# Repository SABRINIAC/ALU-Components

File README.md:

# ALU Modules

| What it is

This project is the collection of PCB that make up all of the Intel 8080 (Which is what my CPU is based on) ALU's functionality. \
It contains modules for an 8 bit adder, subtractor, AND, OR, XOR, rotate left, and rotate right. Also it has a NOT module for the CMA instruction, which inverts all the bits in the accumulator register. \
Also coincidentally there are 8 modules, which will make multiplexing to choose data lines really nice and easy! If I ever decide to create the module for DAA, which I don't have atm because im kinda lazy and I think it'll be seldom used, I can alway make the NOT module not on the multiplex because it is exclusively used to invert the accumulator register for CMA and nothing else.

| Why I made it

Most of my reasoning can be found in the [RAM Module readme](https://github.com/SABRINIAC/DelayLineRAM-ShiftRegister) but aside from that I made this so I can do what CPUs are really good for. Math! These modules alone, making up the ALU, accounts for 96 out of the 255 instructions my CPU needs. Over a third at 37.6%! \
I don't think another project will get even close to implementing that many instructions! They would need a combination of making registers, and routing on the motherboard; which tbf the ALU also needs that. \

Also, making a computer out of pure transistors sounds really cool! Getting to learn how to make logic gates with them was fun, but I don't think I've fully committed how they precisely work to my brain yet... maybe later on in this project.

| Pictures

| BOM + Quantity

You can see a greater breakdown in BOM.md, but here the table breakdown
| Part Name | Count |
|-----------|-------|
| 1x2 Male Pin Headers | 99 |
| 2N2222 NPN Transistors | 432 |
| 1kΩ Resistor 0603 SMD | 670 |
| Adder PCB | 1 |
| Subtractor PCB | 1 |
| AND PCB | 1 |
| XOR PCB | 1 |
| OR PCB | 1 |
| NOT PCB | 1 |
| Rotate Right PCB | 1 |
| Rotate Left PCB | 1 |

# Built Modules

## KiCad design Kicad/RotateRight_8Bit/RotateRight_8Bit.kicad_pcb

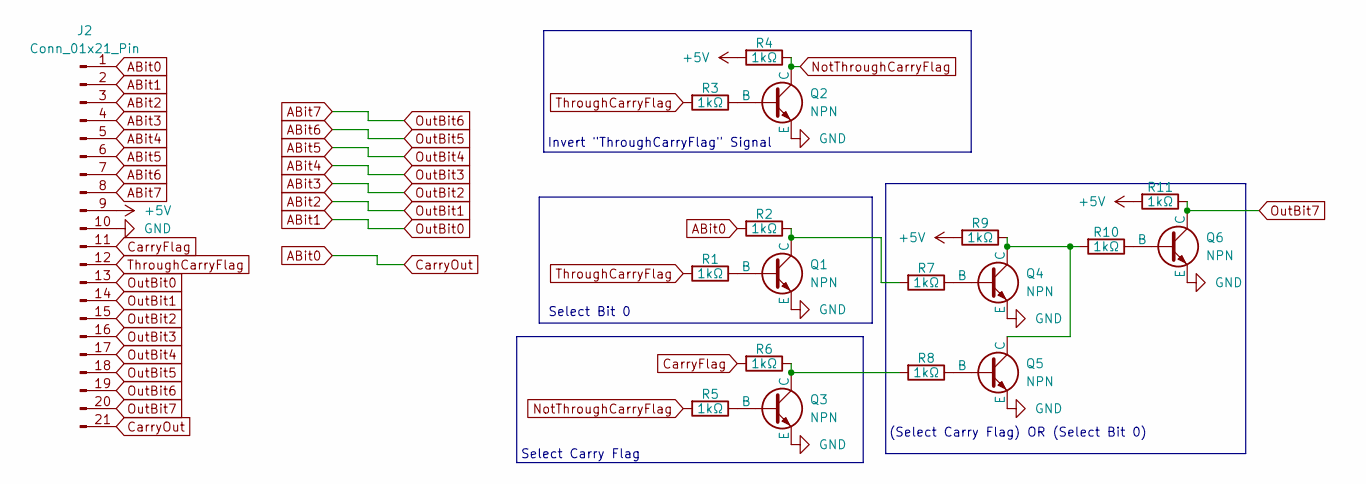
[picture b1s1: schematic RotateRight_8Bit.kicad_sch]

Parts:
J2: Conn_01x21_Pin; PinHeader_1x21_P2.54mm_Horizontal
Q1, Q2, Q3, Q4, Q5, Q6: NPN; TO-92
R1, R2, R3, R4, R5, R6, R7, R8, R9, R10, R11: 1kΩ; R_0603_1608Metric

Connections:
+5V: J2.9, R4.2, R9.2, R11.2
ABit0: J2.1, J2.21, R2.2
ABit1: J2.2, J2.13
ABit2: J2.3, J2.14
ABit3: J2.4, J2.15
ABit4: J2.5, J2.16
ABit5: J2.6, J2.17
ABit6: J2.7, J2.18
ABit7: J2.8, J2.19
CarryFlag: J2.11, R6.2
GND: J2.10, Q1.3 (E), Q2.3 (E), Q3.3 (E), Q4.3 (E), Q5.3 (E), Q6.3 (E)
unnamed: Q1.2 (B), R1.1
unnamed: Q1.1 (C), R2.1, R7.2
unnamed: Q2.2 (B), R3.1
unnamed: Q3.2 (B), R5.1
unnamed: Q3.1 (C), R6.1, R8.2
unnamed: Q4.2 (B), R7.1
unnamed: Q4.1 (C), Q5.1 (C), R9.1, R10.2
unnamed: Q5.2 (B), R8.1
unnamed: Q6.2 (B), R10.1
NotThroughCarryFlag: Q2.1 (C), R4.1, R5.2
OutBit7: J2.20, Q6.1 (C), R11.1
ThroughCarryFlag: J2.12, R1.2, R3.2

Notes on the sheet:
(Select Carry Flag) OR (Select Bit 0)
Select Bit 0
Select Carry Flag
Invert "ThroughCarryFlag" Signal

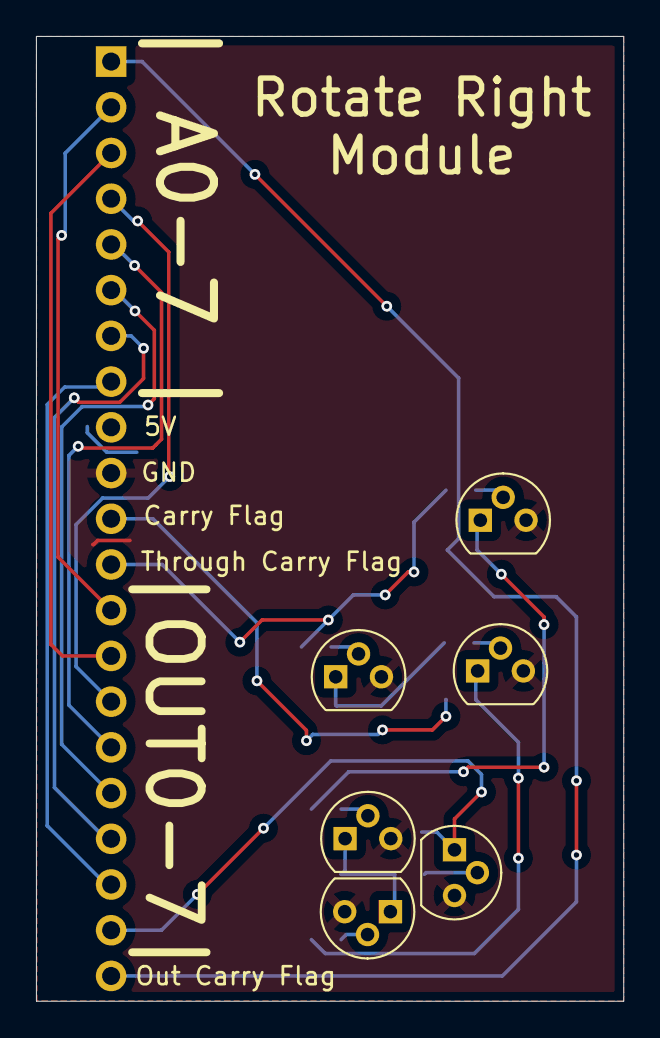
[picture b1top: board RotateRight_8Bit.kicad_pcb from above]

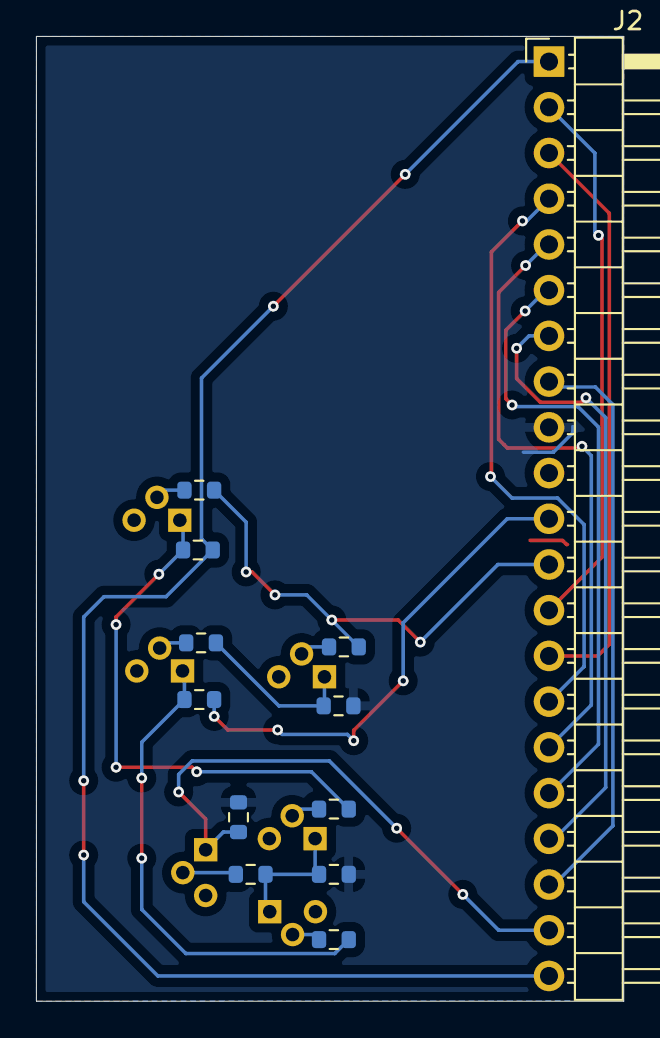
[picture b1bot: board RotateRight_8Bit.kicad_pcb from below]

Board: 2 copper layers, 32.6 x 53.6 mm, 18 parts (12 on the bottom side), 23 nets.

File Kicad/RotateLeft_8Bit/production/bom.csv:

Designator,Footprint,Quantity,Value,LCSC Part #
J2,PinHeader_1x21_P2.54mm_Horizontal,1,Conn_01x21_Pin,
"Q1, Q2, Q3, Q4, Q5, Q6",TO-92,6,NPN,
"R1, R10, R11, R2, R3, R4, R5, R6, R7, R8, R9",0603,11,1kΩ,

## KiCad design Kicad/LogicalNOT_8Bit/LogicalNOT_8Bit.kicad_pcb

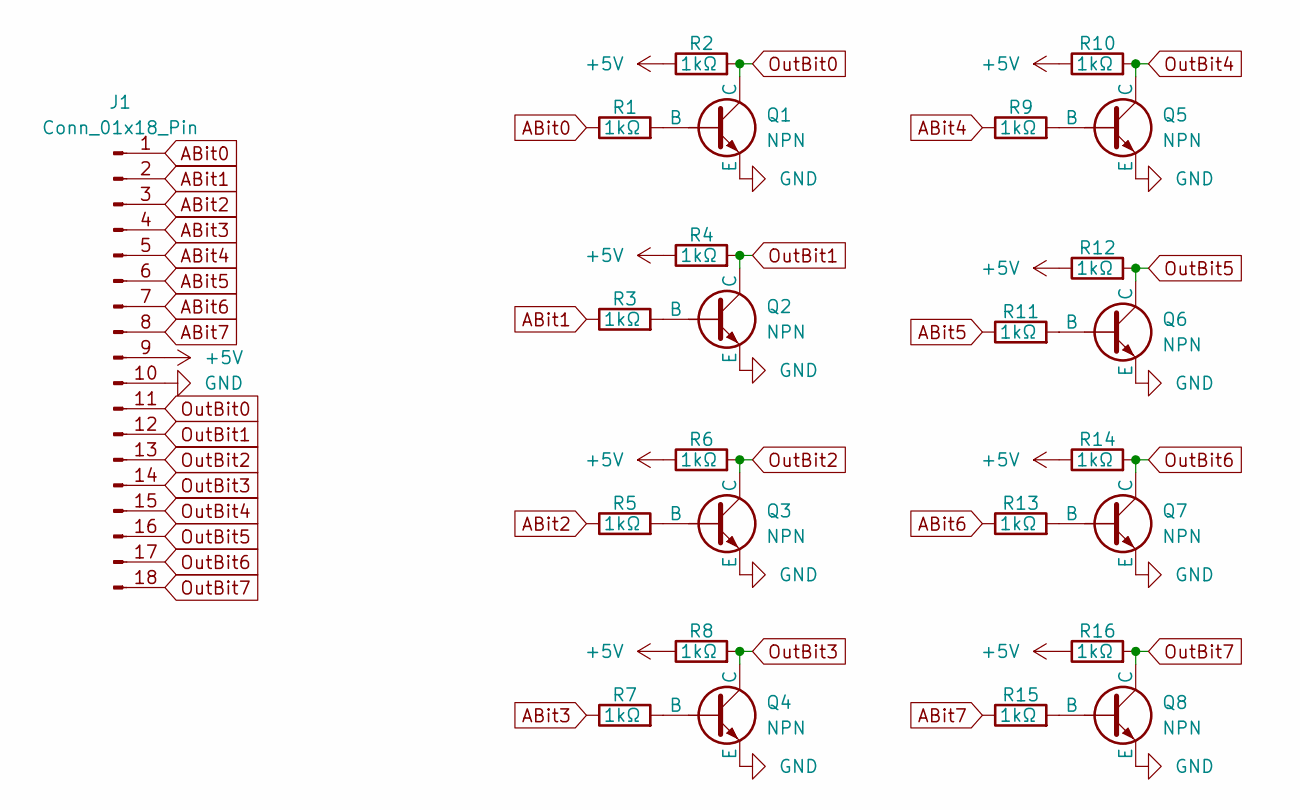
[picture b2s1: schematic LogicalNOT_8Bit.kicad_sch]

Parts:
J1: Conn_01x18_Pin; PinHeader_1x18_P2.54mm_Horizontal
Q1, Q2, Q3, Q4, Q5, Q6, Q7, Q8: NPN; TO-92
R1, R2, R3, R4, R5, R6, R7, R8, R9, R10, R11, R12, R13, R14, R15, R16: 1kΩ; R_0603_1608Metric

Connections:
+5V: J1.9, R2.1, R4.1, R6.1, R8.1, R10.1, R12.1, R14.1, R16.1
ABit0: J1.1, R1.1
ABit1: J1.2, R3.1
ABit2: J1.3, R5.1
ABit3: J1.4, R7.1
ABit4: J1.5, R9.1
ABit5: J1.6, R11.1
ABit6: J1.7, R13.1
ABit7: J1.8, R15.1
GND: J1.10, Q1.3 (E), Q2.3 (E), Q3.3 (E), Q4.3 (E), Q5.3 (E), Q6.3 (E), Q7.3 (E), Q8.3 (E)
unnamed: Q1.2 (B), R1.2
unnamed: Q2.2 (B), R3.2
unnamed: Q3.2 (B), R5.2
unnamed: Q4.2 (B), R7.2
unnamed: Q5.2 (B), R9.2
unnamed: Q6.2 (B), R11.2
unnamed: Q7.2 (B), R13.2
unnamed: Q8.2 (B), R15.2
OutBit0: J1.11, Q1.1 (C), R2.2
OutBit1: J1.12, Q2.1 (C), R4.2
OutBit2: J1.13, Q3.1 (C), R6.2
OutBit3: J1.14, Q4.1 (C), R8.2
OutBit4: J1.15, Q5.1 (C), R10.2
OutBit5: J1.16, Q6.1 (C), R12.2
OutBit6: J1.17, Q7.1 (C), R14.2
OutBit7: J1.18, Q8.1 (C), R16.2

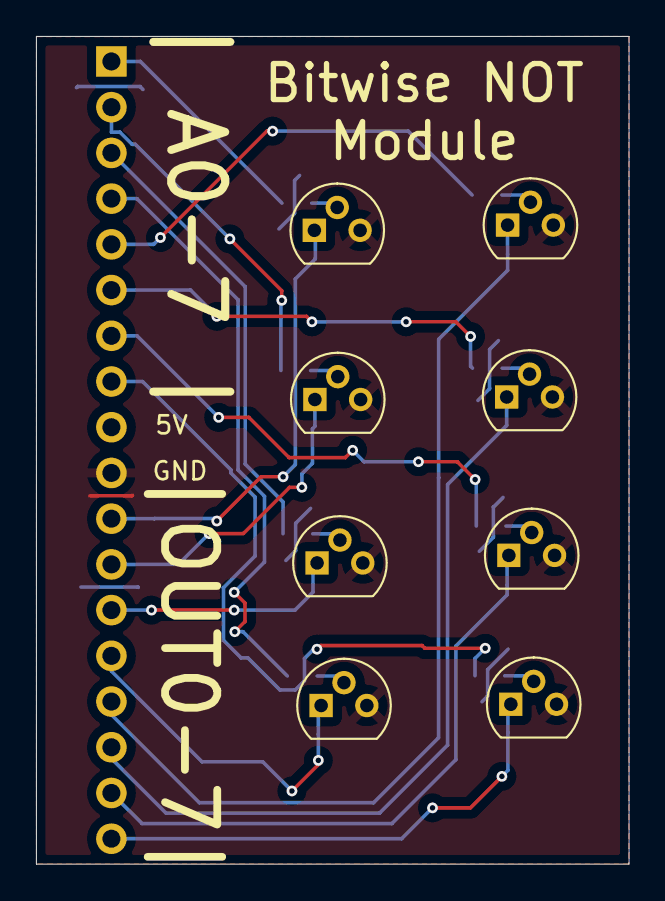
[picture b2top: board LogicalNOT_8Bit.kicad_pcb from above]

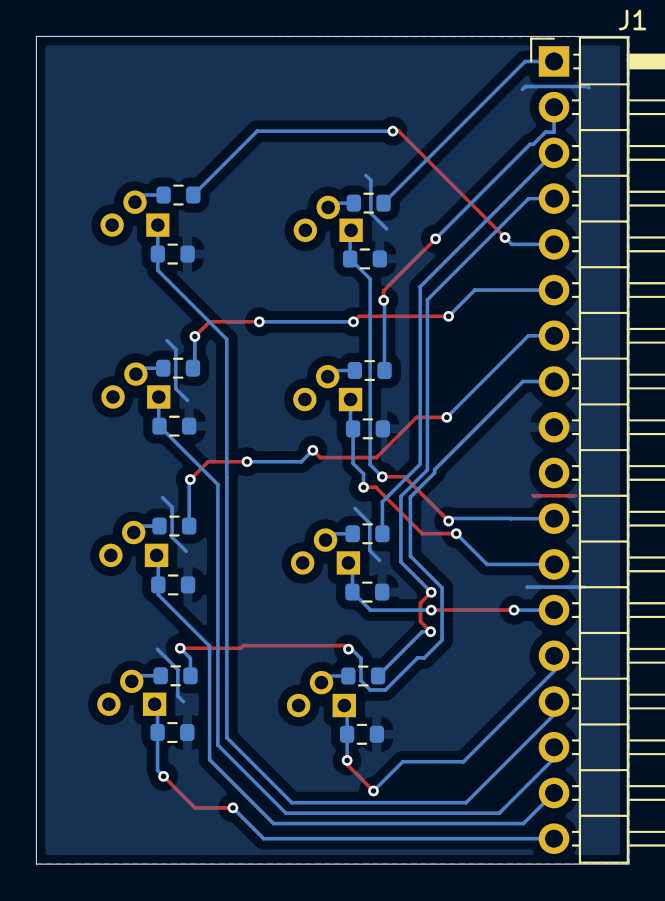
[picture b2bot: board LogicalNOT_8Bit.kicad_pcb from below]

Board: 2 copper layers, 32.9 x 46.0 mm, 25 parts (17 on the bottom side), 26 nets.

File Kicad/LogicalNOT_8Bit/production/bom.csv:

Designator,Footprint,Quantity,Value,LCSC Part #
J1,PinHeader_1x18_P2.54mm_Horizontal,1,Conn_01x18_Pin,
"Q1, Q2, Q3, Q4, Q5, Q6, Q7, Q8",TO-92,8,NPN,
"R1, R10, R11, R12, R13, R14, R15, R16, R2, R3, R4, R5, R6, R7, R8, R9",0603,16,1kΩ,

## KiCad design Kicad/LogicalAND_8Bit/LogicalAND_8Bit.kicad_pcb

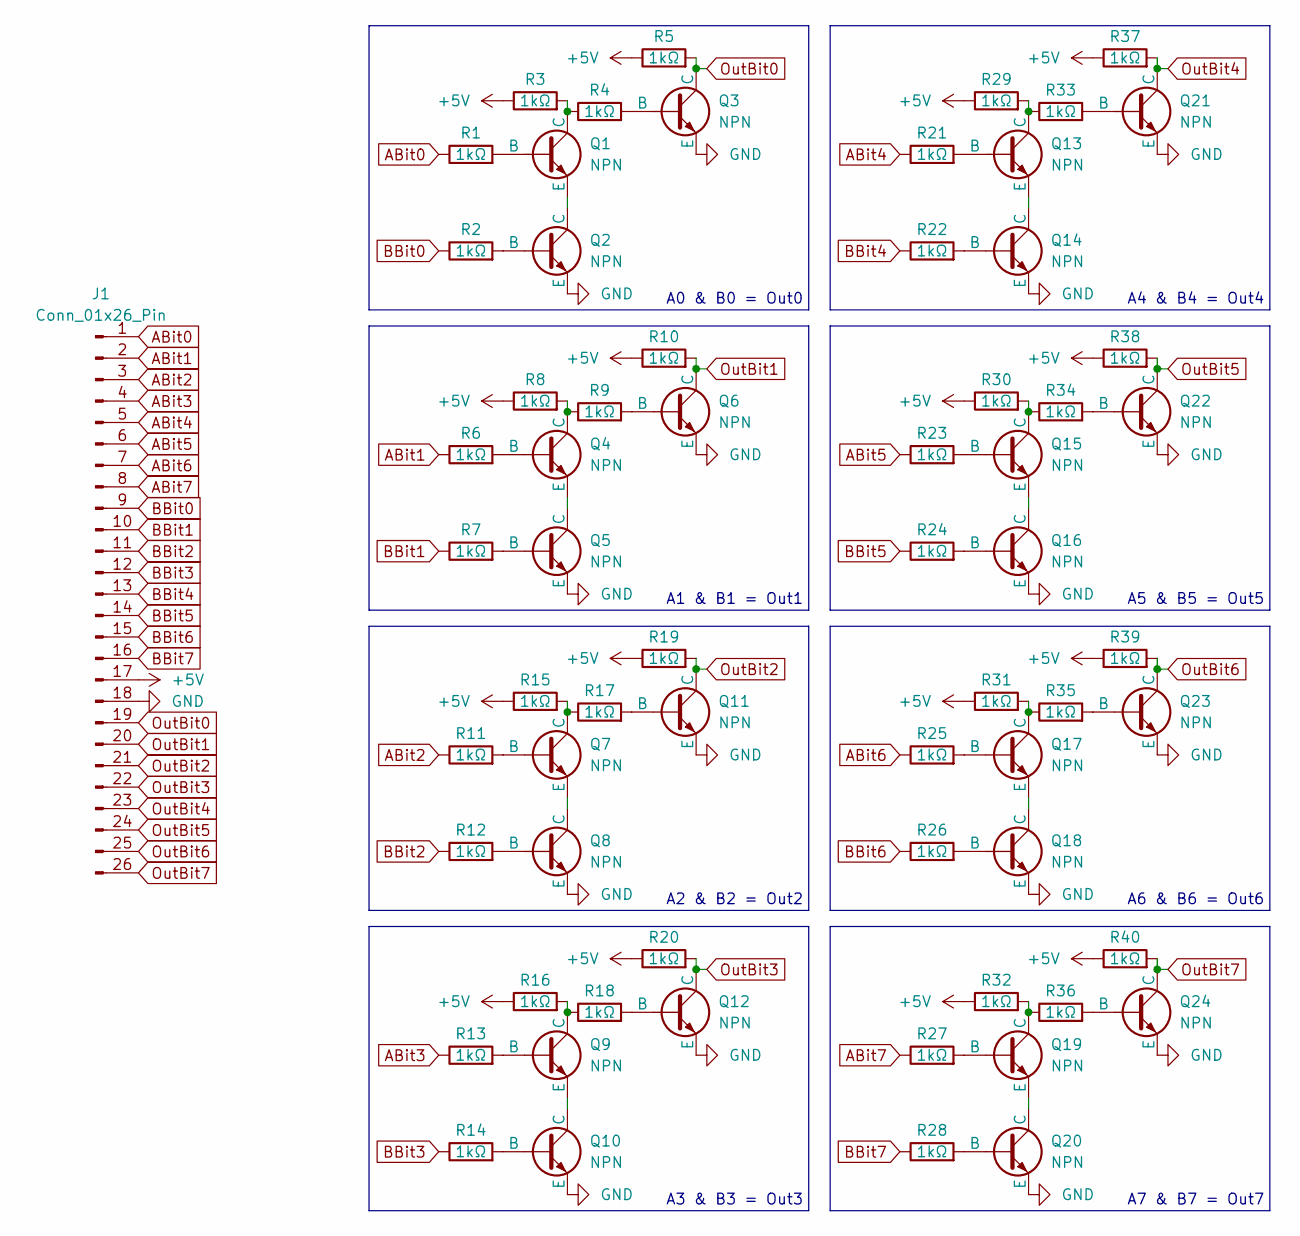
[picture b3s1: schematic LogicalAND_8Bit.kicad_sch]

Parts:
J1: Conn_01x26_Pin; PinHeader_1x26_P2.54mm_Horizontal
Q1, Q2, Q3, Q4, Q5, Q6, Q7, Q8, Q9, Q10, Q11, Q12, Q13, Q14, Q15, Q16, Q17, Q18, Q19, Q20, Q21, Q22, Q23, Q24: NPN; TO-92
R1, R2, R3, R4, R5, R6, R7, R8, R9, R10, R11, R12, R13, R14, R15, R16, R17, R18, R19, R20, R21, R22, R23, R24, R25, R26, R27, R28, R29, R30, R31, R32, R33, R34, R35, R36, R37, R38, R39, R40: 1kΩ; R_0603_1608Metric

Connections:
+5V: J1.17, R3.1, R5.1, R8.1, R10.1, R15.1, R16.1, R19.1, R20.1, R29.1, R30.1, R31.1, R32.1, R37.1, R38.1, R39.1, R40.1
ABit0: J1.1, R1.1
ABit1: J1.2, R6.1
ABit2: J1.3, R11.1
ABit3: J1.4, R13.1
ABit4: J1.5, R21.1
ABit5: J1.6, R23.1
ABit6: J1.7, R25.1
ABit7: J1.8, R27.1
BBit0: J1.9, R2.1
BBit1: J1.10, R7.1
BBit2: J1.11, R12.1
BBit3: J1.12, R14.1
BBit4: J1.13, R22.1
BBit5: J1.14, R24.1
BBit6: J1.15, R26.1
BBit7: J1.16, R28.1
GND: J1.18, Q2.3 (E), Q3.3 (E), Q5.3 (E), Q6.3 (E), Q8.3 (E), Q10.3 (E), Q11.3 (E), Q12.3 (E), Q14.3 (E), Q16.3 (E), Q18.3 (E), Q20.3 (E), Q21.3 (E), Q22.3 (E), Q23.3 (E), Q24.3 (E)
unnamed: Q1.2 (B), R1.2
unnamed: Q1.1 (C), R3.2, R4.1
unnamed: Q1.3 (E), Q2.1 (C)
unnamed: Q2.2 (B), R2.2
unnamed: Q3.2 (B), R4.2
unnamed: Q4.2 (B), R6.2
unnamed: Q4.1 (C), R8.2, R9.1
unnamed: Q4.3 (E), Q5.1 (C)
unnamed: Q5.2 (B), R7.2
unnamed: Q6.2 (B), R9.2
unnamed: Q7.2 (B), R11.2
unnamed: Q7.1 (C), R15.2, R17.1
unnamed: Q7.3 (E), Q8.1 (C)
unnamed: Q8.2 (B), R12.2
unnamed: Q9.2 (B), R13.2
unnamed: Q9.1 (C), R16.2, R18.1
unnamed: Q10.2 (B), R14.2
unnamed: Q9.3 (E), Q10.1 (C)
unnamed: Q11.2 (B), R17.2
unnamed: Q12.2 (B), R18.2
unnamed: Q13.2 (B), R21.2
unnamed: Q13.1 (C), R29.2, R33.1
unnamed: Q13.3 (E), Q14.1 (C)
unnamed: Q14.2 (B), R22.2
unnamed: Q15.2 (B), R23.2
unnamed: Q15.1 (C), R30.2, R34.1
unnamed: Q15.3 (E), Q16.1 (C)
unnamed: Q16.2 (B), R24.2
unnamed: Q17.2 (B), R25.2
unnamed: Q17.1 (C), R31.2, R35.1
unnamed: Q17.3 (E), Q18.1 (C)
unnamed: Q18.2 (B), R26.2
unnamed: Q19.2 (B), R27.2
unnamed: Q19.1 (C), R32.2, R36.1
unnamed: Q19.3 (E), Q20.1 (C)
unnamed: Q20.2 (B), R28.2
unnamed: Q21.2 (B), R33.2
unnamed: Q22.2 (B), R34.2
unnamed: Q23.2 (B), R35.2
unnamed: Q24.2 (B), R36.2
OutBit0: J1.19, Q3.1 (C), R5.2
OutBit1: J1.20, Q6.1 (C), R10.2
OutBit2: J1.21, Q11.1 (C), R19.2
OutBit3: J1.22, Q12.1 (C), R20.2
OutBit4: J1.23, Q21.1 (C), R37.2
OutBit5: J1.24, Q22.1 (C), R38.2
OutBit6: J1.25, Q23.1 (C), R39.2
OutBit7: J1.26, Q24.1 (C), R40.2

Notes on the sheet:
A7 & B7 = Out7
A4 & B4 = Out4
A6 & B6 = Out6
A0 & B0 = Out0
A3 & B3 = Out3
A2 & B2 = Out2
A1 & B1 = Out1
A5 & B5 = Out5

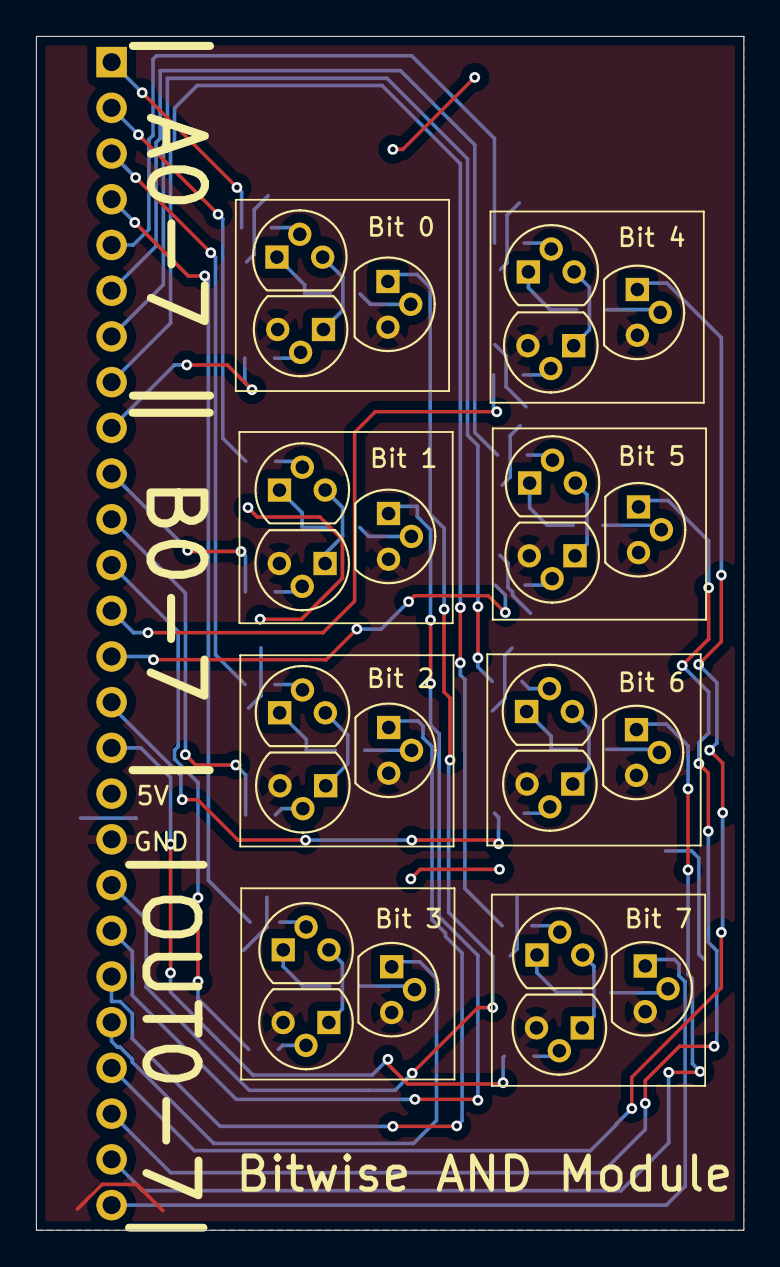
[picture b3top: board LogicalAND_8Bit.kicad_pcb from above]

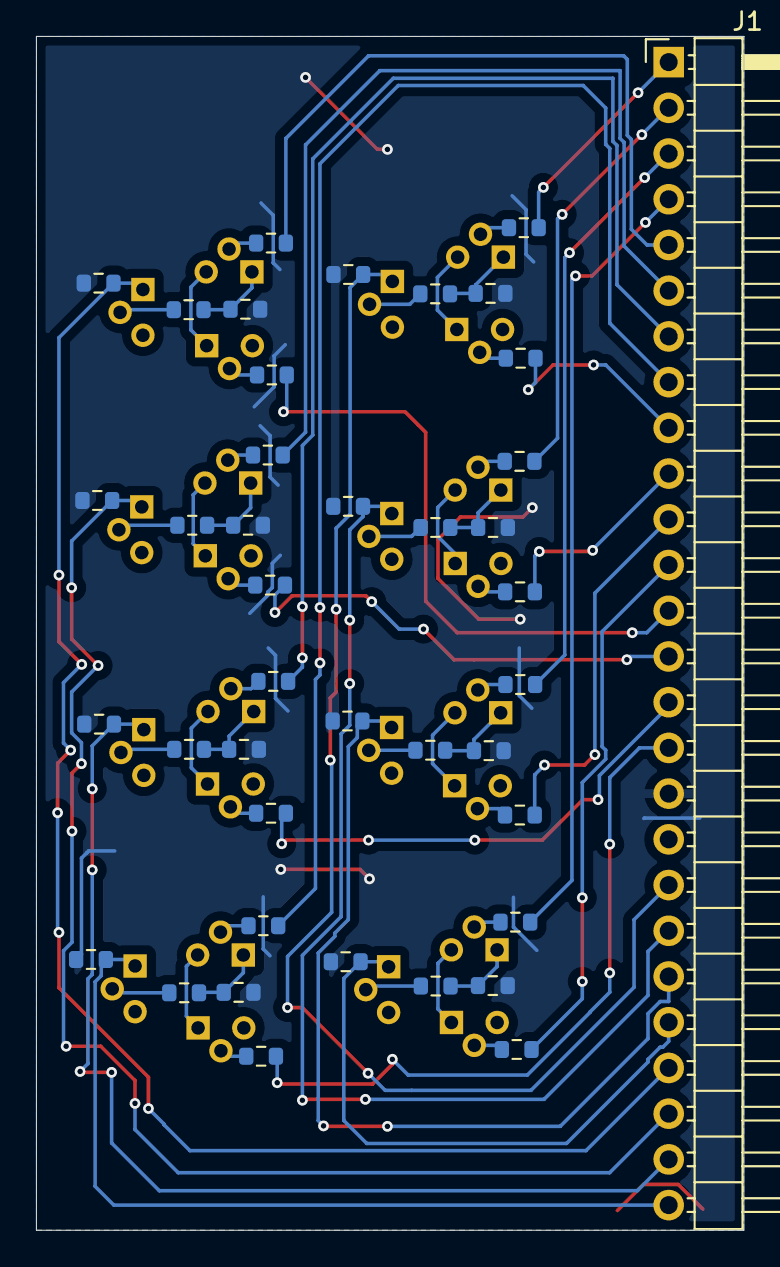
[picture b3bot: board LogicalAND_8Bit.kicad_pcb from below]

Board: 2 copper layers, 39.3 x 66.3 mm, 65 parts (41 on the bottom side), 66 nets.

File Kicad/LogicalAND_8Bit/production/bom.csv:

Designator,Footprint,Quantity,Value,LCSC Part #
J1,PinHeader_1x26_P2.54mm_Horizontal,1,Conn_01x26_Pin,
"Q1, Q10, Q11, Q12, Q13, Q14, Q15, Q16, Q17, Q18, Q19, Q2, Q20, Q21, Q22, Q23, Q24, Q3, Q4, Q5, Q6, Q7, Q8, Q9",TO-92,24,NPN,
"R1, R10, R11, R12, R13, R14, R15, R16, R17, R18, R19, R2, R20, R21, R22, R23, R24, R25, R26, R27, R28, R29, R3, R30, R31, R32, R33, R34, R35, R36, R37, R38, R39, R4, R40, R5, R6, R7, R8, R9",0603,40,1kΩ,

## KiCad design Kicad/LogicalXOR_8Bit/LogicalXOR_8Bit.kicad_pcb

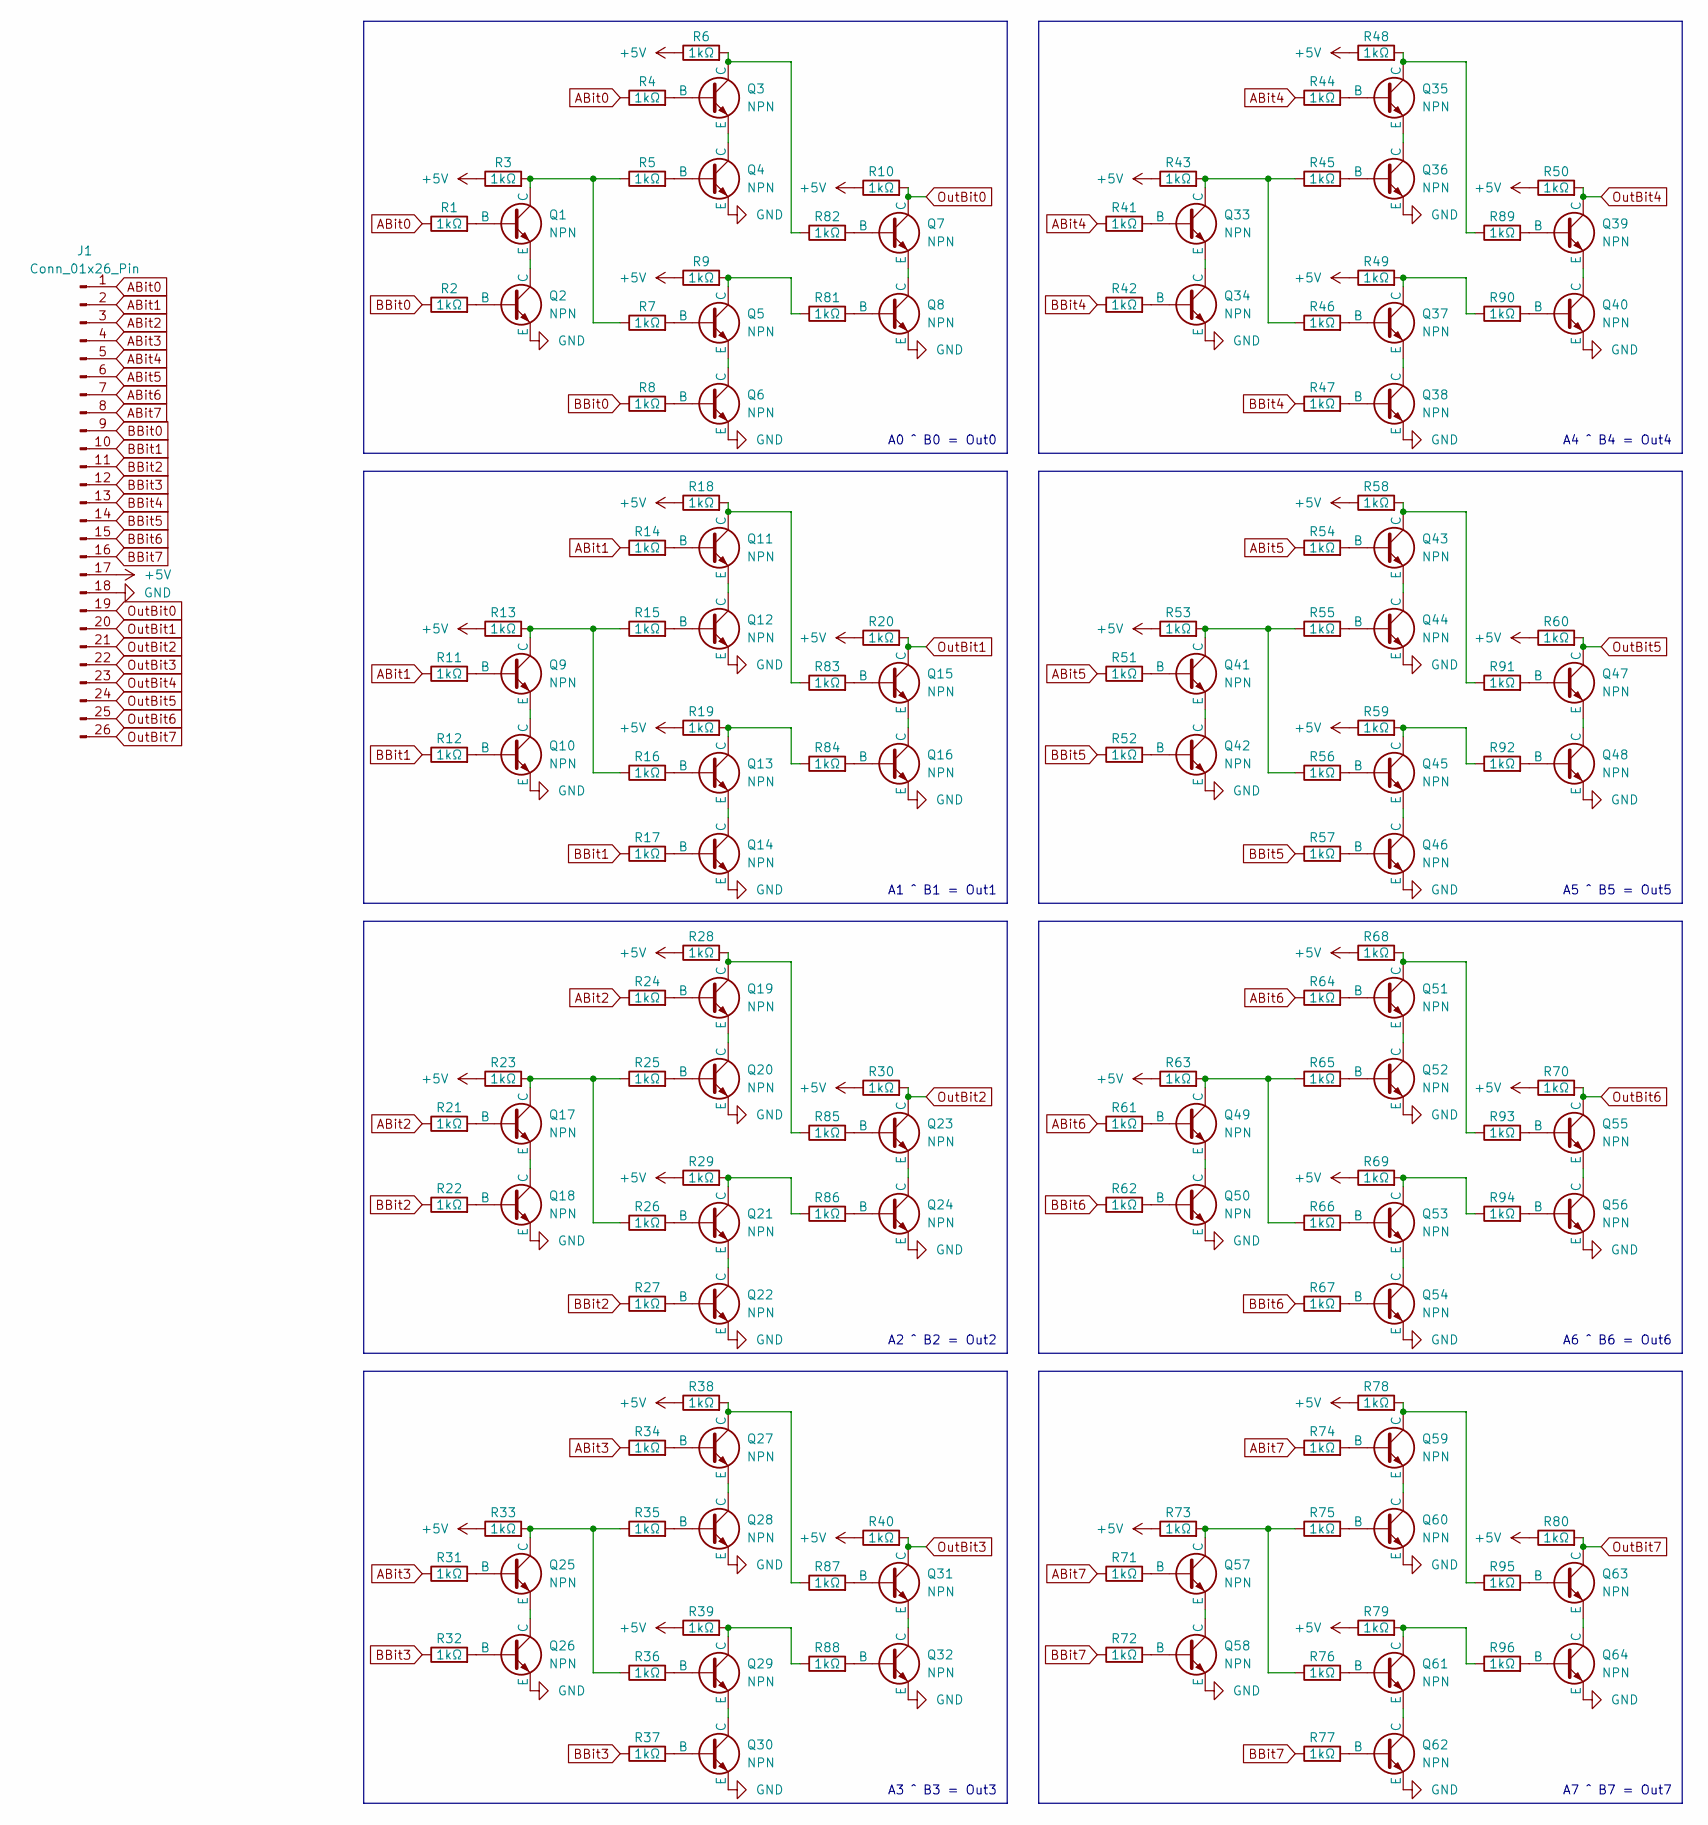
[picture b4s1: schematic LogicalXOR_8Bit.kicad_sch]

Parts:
J1: Conn_01x26_Pin; PinHeader_1x26_P2.54mm_Horizontal
Q1, Q2, Q3, Q4, Q5, Q6, Q7, Q8, Q9, Q10, Q11, Q12, Q13, Q14, Q15, Q16, Q17, Q18, Q19, Q20, Q21, Q22, Q23, Q24, Q25, Q26, Q27, Q28, Q29, Q30, Q31, Q32, Q33, Q34, Q35, Q36, Q37, Q38, Q39, Q40, Q41, Q42, Q43, Q44, Q45, Q46, Q47, Q48, Q49, Q50, Q51, Q52, Q53, Q54, Q55, Q56, Q57, Q58, Q59, Q60, Q61, Q62, Q63, Q64: NPN; TO-92
R1, R2, R3, R4, R5, R6, R7, R8, R9, R10, R11, R12, R13, R14, R15, R16, R17, R18, R19, R20, R21, R22, R23, R24, R25, R26, R27, R28, R29, R30, R31, R32, R33, R34, R35, R36, R37, R38, R39, R40, R41, R42, R43, R44, R45, R46, R47, R48, R49, R50, R51, R52, R53, R54, R55, R56, R57, R58, R59, R60, R61, R62, R63, R64, R65, R66, R67, R68, R69, R70, R71, R72, R73, R74, R75, R76, R77, R78, R79, R80, R81, R82, R83, R84, R85, R86, R87, R88, R89, R90, R91, R92, R93, R94, R95, R96: 1kΩ; R_0603_1608Metric

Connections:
+5V: J1.17, R3.1, R6.1, R9.1, R10.1, R13.1, R18.1, R19.1, R20.1, R23.1, R28.1, R29.1, R30.1, R33.1, R38.1, R39.1, R40.1, R43.1, R48.1, R49.1, R50.1, R53.1, R58.1, R59.1, R60.1, R63.1, R68.1, R69.1, R70.1, R73.1, R78.1, R79.1, R80.1
ABit0: J1.1, R1.1, R4.1
ABit1: J1.2, R11.1, R14.1
ABit2: J1.3, R21.1, R24.1
ABit3: J1.4, R31.1, R34.1
ABit4: J1.5, R41.1, R44.1
ABit5: J1.6, R51.1, R54.1
ABit6: J1.7, R61.1, R64.1
ABit7: J1.8, R71.1, R74.1
BBit0: J1.9, R2.1, R8.1
BBit1: J1.10, R12.1, R17.1
BBit2: J1.11, R22.1, R27.1
BBit3: J1.12, R32.1, R37.1
BBit4: J1.13, R42.1, R47.1
BBit5: J1.14, R52.1, R57.1
BBit6: J1.15, R62.1, R67.1
BBit7: J1.16, R72.1, R77.1
GND: J1.18, Q2.3 (E), Q4.3 (E), Q6.3 (E), Q8.3 (E), Q10.3 (E), Q12.3 (E), Q14.3 (E), Q16.3 (E), Q18.3 (E), Q20.3 (E), Q22.3 (E), Q24.3 (E), Q26.3 (E), Q28.3 (E), Q30.3 (E), Q32.3 (E), Q34.3 (E), Q36.3 (E), Q38.3 (E), Q40.3 (E), Q42.3 (E), Q44.3 (E), Q46.3 (E), Q48.3 (E), Q50.3 (E), Q52.3 (E), Q54.3 (E), Q56.3 (E), Q58.3 (E), Q60.3 (E), Q62.3 (E), Q64.3 (E)
unnamed: Q1.2 (B), R1.2
unnamed: Q1.1 (C), R3.2, R5.1, R7.1
unnamed: Q1.3 (E), Q2.1 (C)
unnamed: Q2.2 (B), R2.2
unnamed: Q3.2 (B), R4.2
unnamed: Q3.1 (C), R6.2, R82.1
unnamed: Q3.3 (E), Q4.1 (C)
unnamed: Q4.2 (B), R5.2
unnamed: Q5.2 (B), R7.2
unnamed: Q5.1 (C), R9.2, R81.1
unnamed: Q5.3 (E), Q6.1 (C)
unnamed: Q6.2 (B), R8.2
unnamed: Q7.2 (B), R82.2
unnamed: Q7.3 (E), Q8.1 (C)
unnamed: Q8.2 (B), R81.2
unnamed: Q9.2 (B), R11.2
unnamed: Q9.1 (C), R13.2, R15.1, R16.1
unnamed: Q10.2 (B), R12.2
unnamed: Q9.3 (E), Q10.1 (C)
unnamed: Q11.2 (B), R14.2
unnamed: Q11.1 (C), R18.2, R83.1
unnamed: Q11.3 (E), Q12.1 (C)
unnamed: Q12.2 (B), R15.2
unnamed: Q13.2 (B), R16.2
unnamed: Q13.1 (C), R19.2, R84.1
unnamed: Q13.3 (E), Q14.1 (C)
unnamed: Q14.2 (B), R17.2
unnamed: Q15.2 (B), R83.2
unnamed: Q15.3 (E), Q16.1 (C)
unnamed: Q16.2 (B), R84.2
unnamed: Q17.2 (B), R21.2
unnamed: Q17.1 (C), R23.2, R25.1, R26.1
unnamed: Q17.3 (E), Q18.1 (C)
unnamed: Q18.2 (B), R22.2
unnamed: Q19.2 (B), R24.2
unnamed: Q19.1 (C), R28.2, R85.1
unnamed: Q19.3 (E), Q20.1 (C)
unnamed: Q20.2 (B), R25.2
unnamed: Q21.2 (B), R26.2
unnamed: Q21.1 (C), R29.2, R86.1
unnamed: Q21.3 (E), Q22.1 (C)
unnamed: Q22.2 (B), R27.2
unnamed: Q23.2 (B), R85.2
unnamed: Q23.3 (E), Q24.1 (C)
unnamed: Q24.2 (B), R86.2
unnamed: Q25.2 (B), R31.2
unnamed: Q25.1 (C), R33.2, R35.1, R36.1
unnamed: Q25.3 (E), Q26.1 (C)
unnamed: Q26.2 (B), R32.2
unnamed: Q27.2 (B), R34.2
unnamed: Q27.1 (C), R38.2, R87.1
unnamed: Q27.3 (E), Q28.1 (C)
unnamed: Q28.2 (B), R35.2
unnamed: Q29.2 (B), R36.2
unnamed: Q29.1 (C), R39.2, R88.1
unnamed: Q29.3 (E), Q30.1 (C)
unnamed: Q30.2 (B), R37.2
unnamed: Q31.2 (B), R87.2
unnamed: Q31.3 (E), Q32.1 (C)
unnamed: Q32.2 (B), R88.2
unnamed: Q33.2 (B), R41.2
unnamed: Q33.1 (C), R43.2, R45.1, R46.1
unnamed: Q33.3 (E), Q34.1 (C)
unnamed: Q34.2 (B), R42.2
unnamed: Q35.2 (B), R44.2
unnamed: Q35.1 (C), R48.2, R89.1
unnamed: Q35.3 (E), Q36.1 (C)
unnamed: Q36.2 (B), R45.2
unnamed: Q37.2 (B), R46.2
unnamed: Q37.1 (C), R49.2, R90.1
unnamed: Q37.3 (E), Q38.1 (C)
unnamed: Q38.2 (B), R47.2
unnamed: Q39.2 (B), R89.2
unnamed: Q39.3 (E), Q40.1 (C)
unnamed: Q40.2 (B), R90.2
unnamed: Q41.2 (B), R51.2
unnamed: Q41.1 (C), R53.2, R55.1, R56.1
unnamed: Q41.3 (E), Q42.1 (C)
unnamed: Q42.2 (B), R52.2
unnamed: Q43.2 (B), R54.2
unnamed: Q43.1 (C), R58.2, R91.1
unnamed: Q43.3 (E), Q44.1 (C)
unnamed: Q44.2 (B), R55.2
unnamed: Q45.2 (B), R56.2
unnamed: Q45.1 (C), R59.2, R92.1
unnamed: Q45.3 (E), Q46.1 (C)
unnamed: Q46.2 (B), R57.2
unnamed: Q47.2 (B), R91.2
unnamed: Q47.3 (E), Q48.1 (C)
unnamed: Q48.2 (B), R92.2
unnamed: Q49.2 (B), R61.2
unnamed: Q49.1 (C), R63.2, R65.1, R66.1
unnamed: Q49.3 (E), Q50.1 (C)
unnamed: Q50.2 (B), R62.2
unnamed: Q51.2 (B), R64.2
unnamed: Q51.1 (C), R68.2, R93.1
unnamed: Q51.3 (E), Q52.1 (C)
unnamed: Q52.2 (B), R65.2
unnamed: Q53.2 (B), R66.2
unnamed: Q53.1 (C), R69.2, R94.1
unnamed: Q53.3 (E), Q54.1 (C)
unnamed: Q54.2 (B), R67.2
unnamed: Q55.2 (B), R93.2
unnamed: Q55.3 (E), Q56.1 (C)
unnamed: Q56.2 (B), R94.2
unnamed: Q57.2 (B), R71.2
unnamed: Q57.1 (C), R73.2, R75.1, R76.1
unnamed: Q57.3 (E), Q58.1 (C)
unnamed: Q58.2 (B), R72.2
unnamed: Q59.2 (B), R74.2
unnamed: Q59.1 (C), R78.2, R95.1
unnamed: Q59.3 (E), Q60.1 (C)
unnamed: Q60.2 (B), R75.2
unnamed: Q61.2 (B), R76.2
unnamed: Q61.1 (C), R79.2, R96.1
unnamed: Q61.3 (E), Q62.1 (C)
unnamed: Q62.2 (B), R77.2
unnamed: Q63.2 (B), R95.2
unnamed: Q63.3 (E), Q64.1 (C)
unnamed: Q64.2 (B), R96.2
OutBit0: J1.19, Q7.1 (C), R10.2
OutBit1: J1.20, Q15.1 (C), R20.2
OutBit2: J1.21, Q23.1 (C), R30.2
OutBit3: J1.22, Q31.1 (C), R40.2
OutBit4: J1.23, Q39.1 (C), R50.2
OutBit5: J1.24, Q47.1 (C), R60.2
OutBit6: J1.25, Q55.1 (C), R70.2
OutBit7: J1.26, Q63.1 (C), R80.2

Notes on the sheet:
A6 ^ B6 = Out6
A7 ^ B7 = Out7
A4 ^ B4 = Out4
A5 ^ B5 = Out5
A1 ^ B1 = Out1
A3 ^ B3 = Out3
A2 ^ B2 = Out2
A0 ^ B0 = Out0

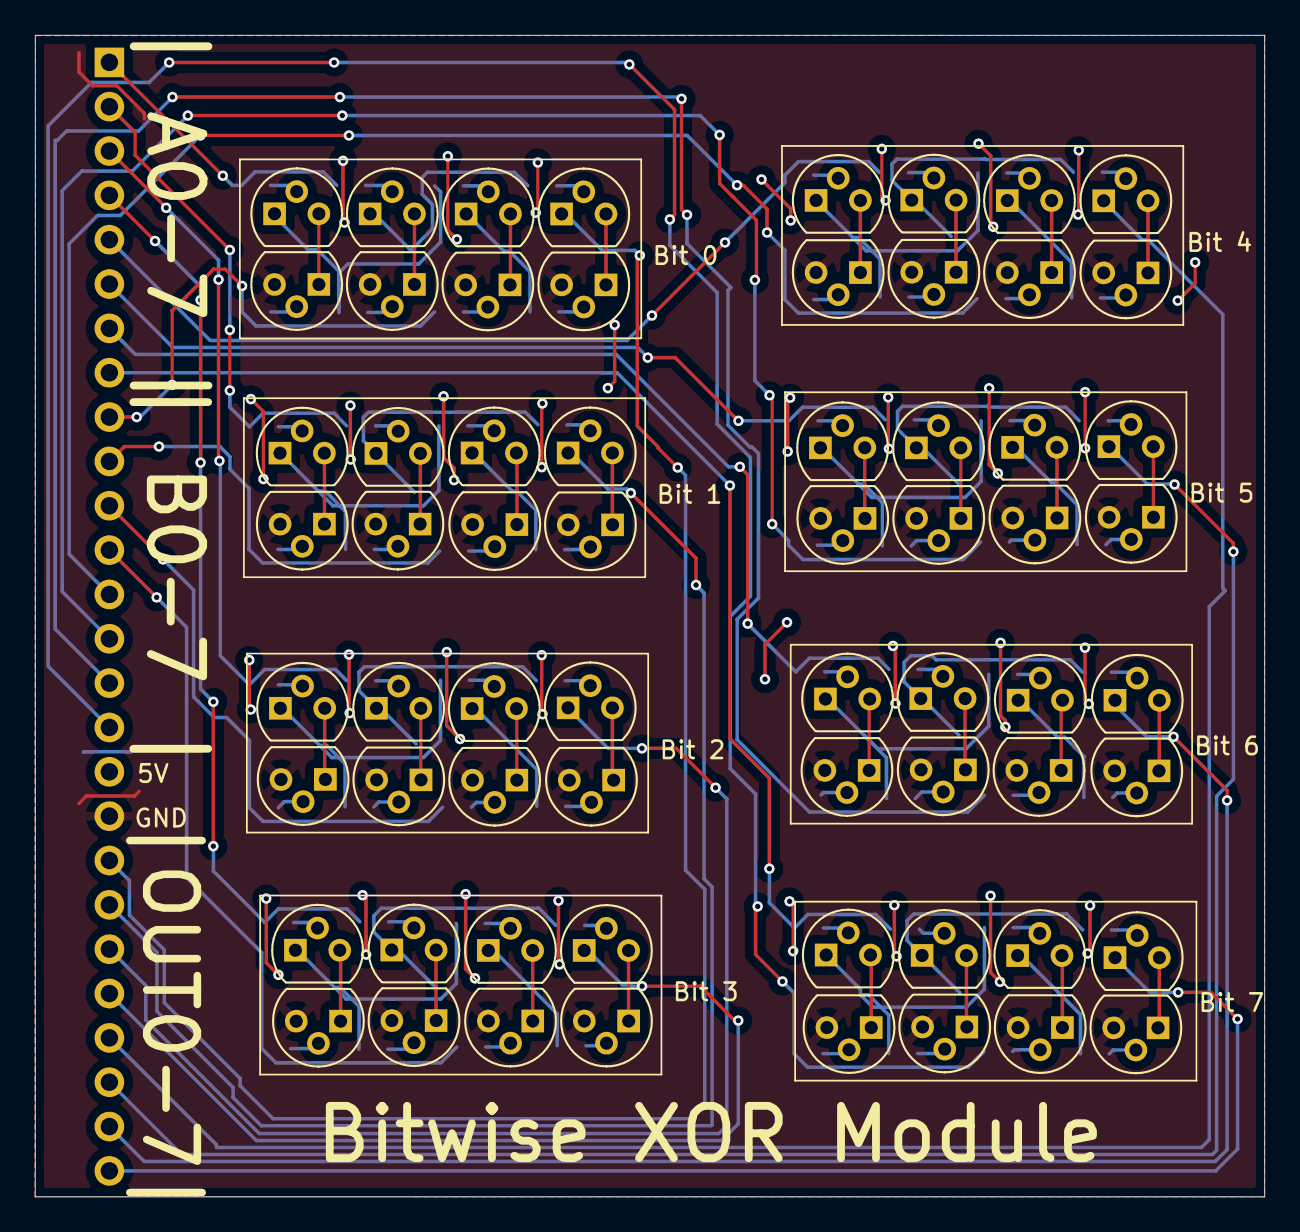
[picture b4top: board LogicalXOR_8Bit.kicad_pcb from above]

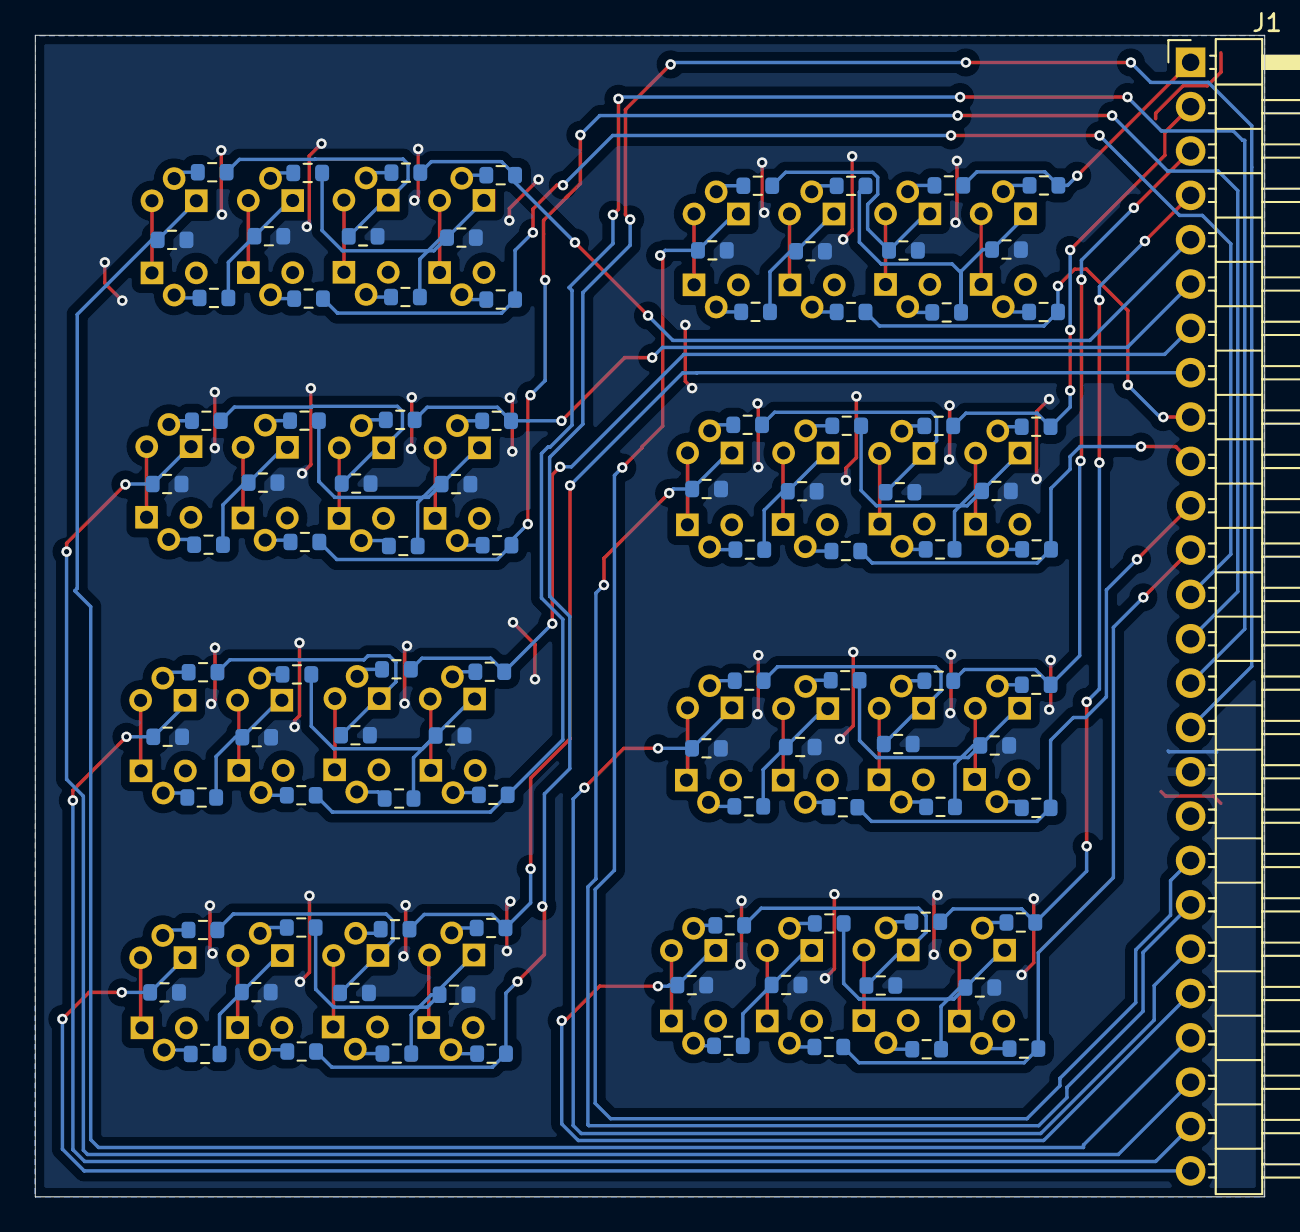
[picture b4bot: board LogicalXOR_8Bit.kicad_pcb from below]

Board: 2 copper layers, 70.4 x 66.5 mm, 161 parts (97 on the bottom side), 146 nets.

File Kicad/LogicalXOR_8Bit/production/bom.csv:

Designator,Footprint,Quantity,Value,LCSC Part #
J1,PinHeader_1x26_P2.54mm_Horizontal,1,Conn_01x26_Pin,
"Q1, Q10, Q11, Q12, Q13, Q14, Q15, Q16, Q17, Q18, Q19, Q2, Q20, Q21, Q22, Q23, Q24, Q25, Q26, Q27, Q28, Q29, Q3, Q30, Q31, Q32, Q33, Q34, Q35, Q36, Q37, Q38, Q39, Q4, Q40, Q41, Q42, Q43, Q44, Q45, Q46, Q47, Q48, Q49, Q5, Q50, Q51, Q52, Q53, Q54, Q55, Q56, Q57, Q58, Q59, Q6, Q60, Q61, Q62, Q63, Q64, Q7, Q8, Q9",TO-92,64,NPN,
"R1, R10, R11, R12, R13, R14, R15, R16, R17, R18, R19, R2, R20, R21, R22, R23, R24, R25, R26, R27, R28, R29, R3, R30, R31, R32, R33, R34, R35, R36, R37, R38, R39, R4, R40, R41, R42, R43, R44, R45, R46, R47, R48, R49, R5, R50, R51, R52, R53, R54, R55, R56, R57, R58, R59, R6, R60, R61, R62, R63, R64, R65, R66, R67, R68, R69, R7, R70, R71, R72, R73, R74, R75, R76, R77, R78, R79, R8, R80, R81, R82, R83, R84, R85, R86, R87, R88, R89, R9, R90, R91, R92, R93, R94, R95, R96",0603,96,1kΩ,
